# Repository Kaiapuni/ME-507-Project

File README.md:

# ME-507-Project
Controls a strip of Neopixel LEDs to respond to the motion of the wearer

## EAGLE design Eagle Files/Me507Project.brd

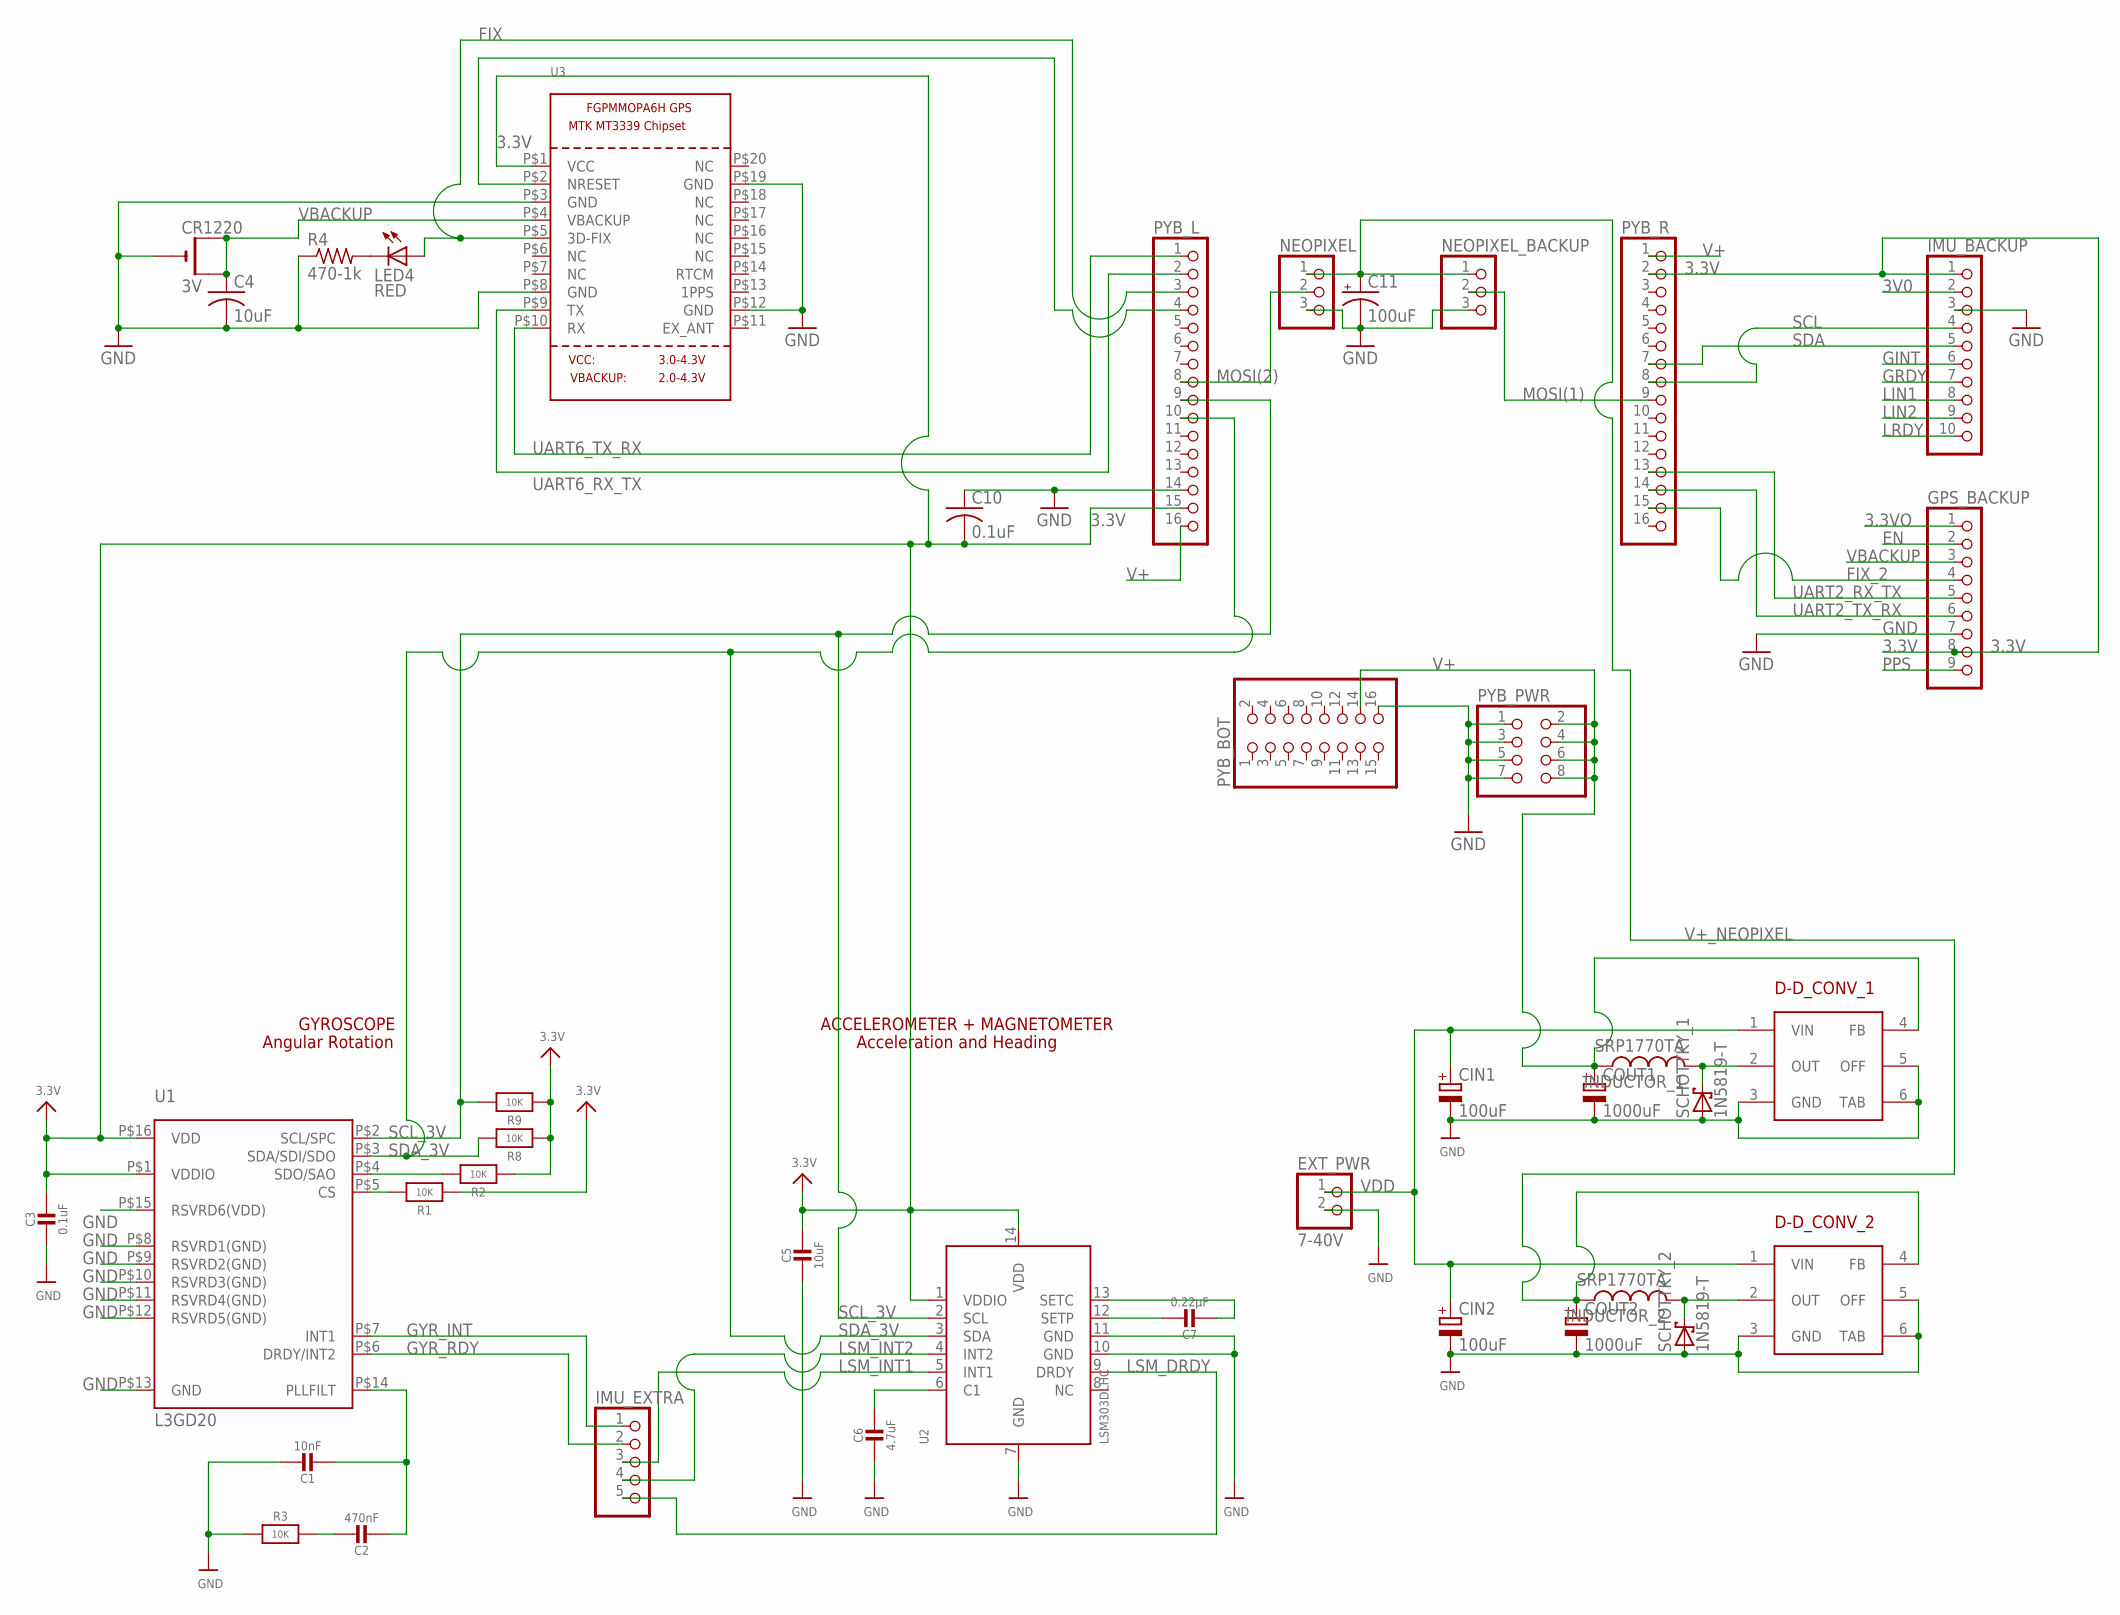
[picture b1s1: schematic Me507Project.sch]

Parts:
C1: 10nF; _0805MP
C2: 470nF; _0805MP
C3: 0.1uF; _0805MP
C4: 10uF; C0805K
C5: 10uF; _0805MP
C6: 4.7uF; _0805MP
C7: 0.22µF; _0805MP
C10: 0.1uF; C0805K
C11: 100uF; 153CLV-0810
CIN1, CIN2: 100uF; UD-8X10_NICHICON
COUT1, COUT2: 1000uF; E5-13
CR1220: 3V; CR1220-SMD
D-D_CONV_1, D-D_CONV_2: AP3003; TO263-5
EXT_PWR: 7-40V; 1X02
GPS_BACKUP: PINHD-1X9; 1X09
IMU_BACKUP: PINHD-1X10; 1X10
IMU_EXTRA: PINHD-1X5; 1X05
INDUCTOR_1, INDUCTOR_2: SRP1770TA
LED4: RED; CHIP-LED0805
NEOPIXEL: PINHD-1X3; 1X03
NEOPIXEL_BACKUP: PINHD-1X3; 1X03
PYB_BOT: PINHD-2X8; 2X08
PYB_L: PINHD-1X16; 1X16
PYB_PWR: PINHD-2X4; 2X04
PYB_R: PINHD-1X16; 1X16
R1, R2, R3, R8, R9: 10K; _0805MP
R4: 470-1k; R0805
SCHOTTKY_1, SCHOTTKY_2: 1N5819-T; DO41-7.6
U1: L3GD20; L3G4200D_LGA16L
U2: LSM303DLHC; LGA14
U3: GPS_FGPMMOPA6H; FGPMMOPA6H

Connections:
3.3V: C3.1, C5.1, C10.2, GPS_BACKUP.8, IMU_BACKUP.1, PYB_L.15, PYB_R.2, R1.1, R2.1, R8.1, R9.1, U1.P$1 (VDDIO), U1.P$16 (VDD), U2.1 (VDDIO), U2.14 (VDD), U3.P$1 (VCC)
3.3VO: GPS_BACKUP.1
3V0: IMU_BACKUP.2
EN: GPS_BACKUP.2
FIX: LED4.A, PYB_L.3, U3.P$5 (3D-FIX)
FIX_2: GPS_BACKUP.4, PYB_R.15
GINT: IMU_BACKUP.6
GND: C1.1, C3.2, C4.2, C5.2, C6.2, C10.1, C11.-, CIN1.-, CIN2.-, COUT1.-, COUT2.-, CR1220.-, D-D_CONV_1.3 (GND), D-D_CONV_1.5 (OFF), D-D_CONV_1.6 (TAB), D-D_CONV_2.3 (GND), D-D_CONV_2.5 (OFF), D-D_CONV_2.6 (TAB), EXT_PWR.2, GPS_BACKUP.7, IMU_BACKUP.3, NEOPIXEL.3, NEOPIXEL_BACKUP.3, PYB_BOT.16, PYB_L.14, PYB_PWR.1, PYB_PWR.3, PYB_PWR.5, PYB_PWR.7, R3.1, R4.1, SCHOTTKY_1.A, SCHOTTKY_2.A, U1.P$8 (RSVRD1(GND)), U1.P$9 (RSVRD2(GND)), U1.P$10 (RSVRD3(GND)), U1.P$11 (RSVRD4(GND)), U1.P$12 (RSVRD5(GND)), U1.P$13 (GND), U1.P$15 (RSVRD6(VDD)), U2.7 (GND), U2.10 (GND), U2.11 (GND), U3.P$3 (GND), U3.P$8 (GND), U3.P$12 (GND), U3.P$19 (GND)
GRDY: IMU_BACKUP.7
GYR_INT: IMU_EXTRA.1, U1.P$7 (INT1)
GYR_RDY: IMU_EXTRA.2, U1.P$6 (DRDY/INT2)
LIN1: IMU_BACKUP.8
LIN2: IMU_BACKUP.9
LRDY: IMU_BACKUP.10
LSM_DRDY: IMU_EXTRA.5, U2.9 (DRDY)
LSM_INT1: IMU_EXTRA.3, U2.5 (INT1)
LSM_INT2: IMU_EXTRA.4, U2.4 (INT2)
MOSI(1): NEOPIXEL_BACKUP.2, PYB_R.9
MOSI(2): NEOPIXEL.2, PYB_L.8
unnamed: R1.2, U1.P$5 (CS)
unnamed: R2.2, U1.P$4 (SDO/SAO)
unnamed: C2.1, R3.2
unnamed: C1.2, C2.2, U1.P$14 (PLLFILT)
unnamed: C7.1, U2.12 (SETP)
unnamed: C6.1, U2.6 (C1)
unnamed: C7.2, U2.13 (SETC)
unnamed: LED4.C, R4.2
unnamed: D-D_CONV_2.2 (OUT), INDUCTOR_2.P$4 (2), SCHOTTKY_2.C
unnamed: PYB_L.4, U3.P$2 (NRESET)
unnamed: D-D_CONV_1.2 (OUT), INDUCTOR_1.P$4 (2), SCHOTTKY_1.C
PPS: GPS_BACKUP.9
SCL: IMU_BACKUP.4, PYB_R.8
SCL_3V: PYB_L.9, R9.2, U1.P$2 (SCL/SPC), U2.2 (SCL)
SDA: IMU_BACKUP.5, PYB_R.7
SDA_3V: PYB_L.10, R8.2, U1.P$3 (SDA/SDI/SDO), U2.3 (SDA)
UART2_RX_TX: GPS_BACKUP.5, PYB_R.13
UART2_TX_RX: GPS_BACKUP.6, PYB_R.14
UART6_RX_TX: PYB_L.2, U3.P$9 (TX)
UART6_TX_RX: PYB_L.1, U3.P$10 (RX)
V+: COUT1.+, D-D_CONV_1.4 (FB), INDUCTOR_1.P$3 (1), PYB_BOT.14, PYB_L.16, PYB_PWR.2, PYB_PWR.4, PYB_PWR.6, PYB_PWR.8, PYB_R.1
V+_NEOPIXEL: C11.+, COUT2.+, D-D_CONV_2.4 (FB), INDUCTOR_2.P$3 (1), NEOPIXEL.1, NEOPIXEL_BACKUP.1
VBACKUP: C4.1, CR1220.+$1 (+), CR1220.+$2 (+1), GPS_BACKUP.3, U3.P$4 (VBACKUP)
VDD: CIN1.+, CIN2.+, D-D_CONV_1.1 (VIN), D-D_CONV_2.1 (VIN), EXT_PWR.1

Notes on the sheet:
GYROSCOPE
Angular Rotation
ACCELEROMETER + MAGNETOMETER
Acceleration and Heading

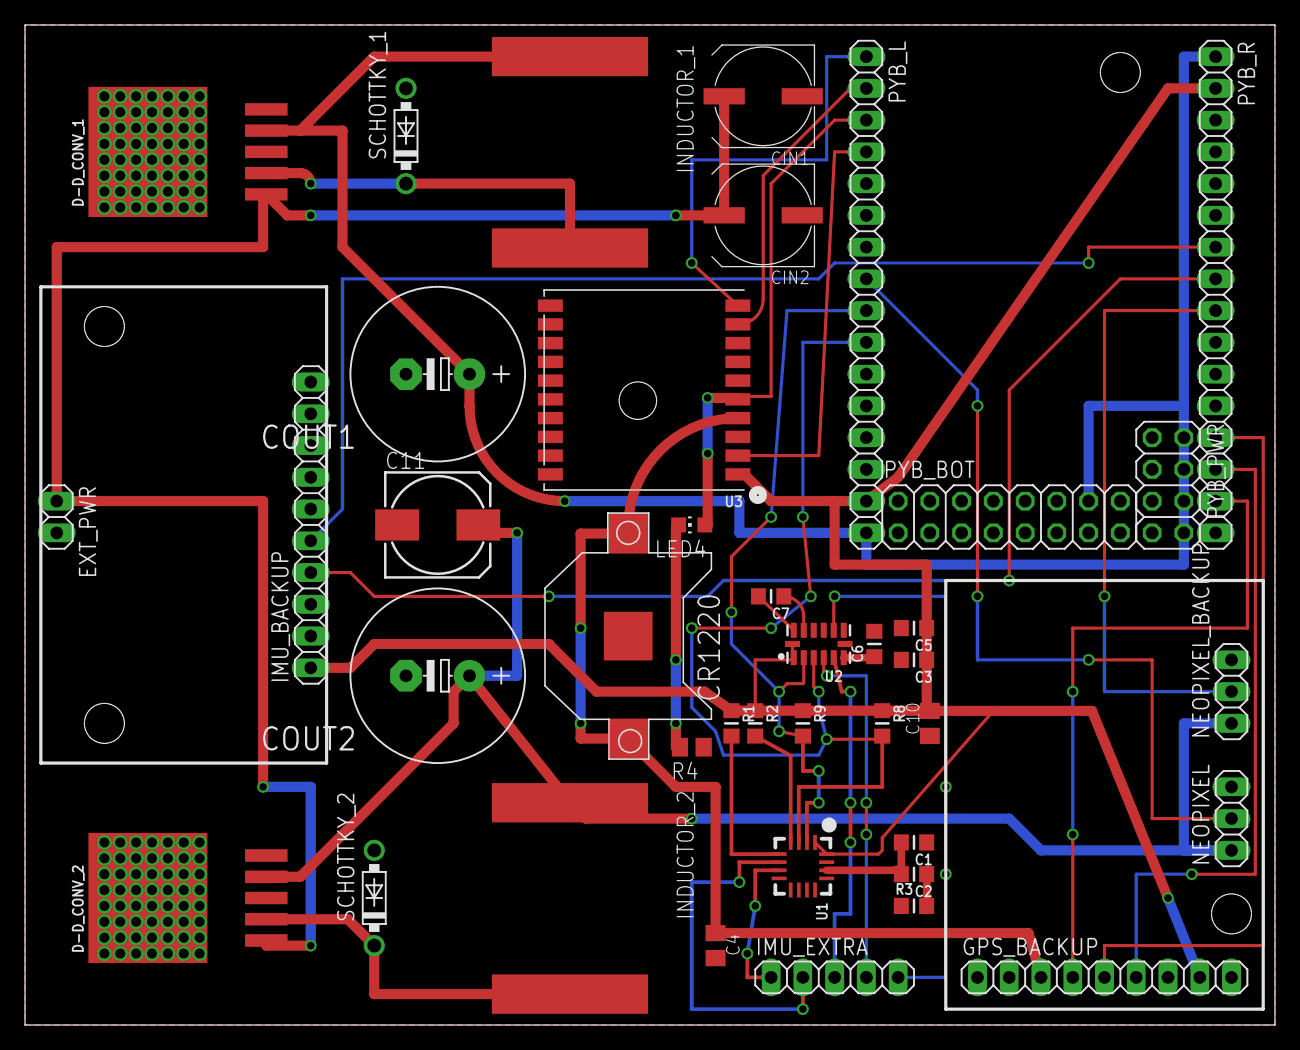
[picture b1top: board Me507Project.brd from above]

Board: 2 copper layers, 100.0 x 80.0 mm, 40 parts (0 on the bottom side), 34 nets.

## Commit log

2018-08-22 Create .gitignore
    Ignore the project report and the eagle files

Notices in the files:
parts and their libraries:
microbuilder: This work is placed in the public domain, and may be freely used for commercial and non-commercial work with the following conditions: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
